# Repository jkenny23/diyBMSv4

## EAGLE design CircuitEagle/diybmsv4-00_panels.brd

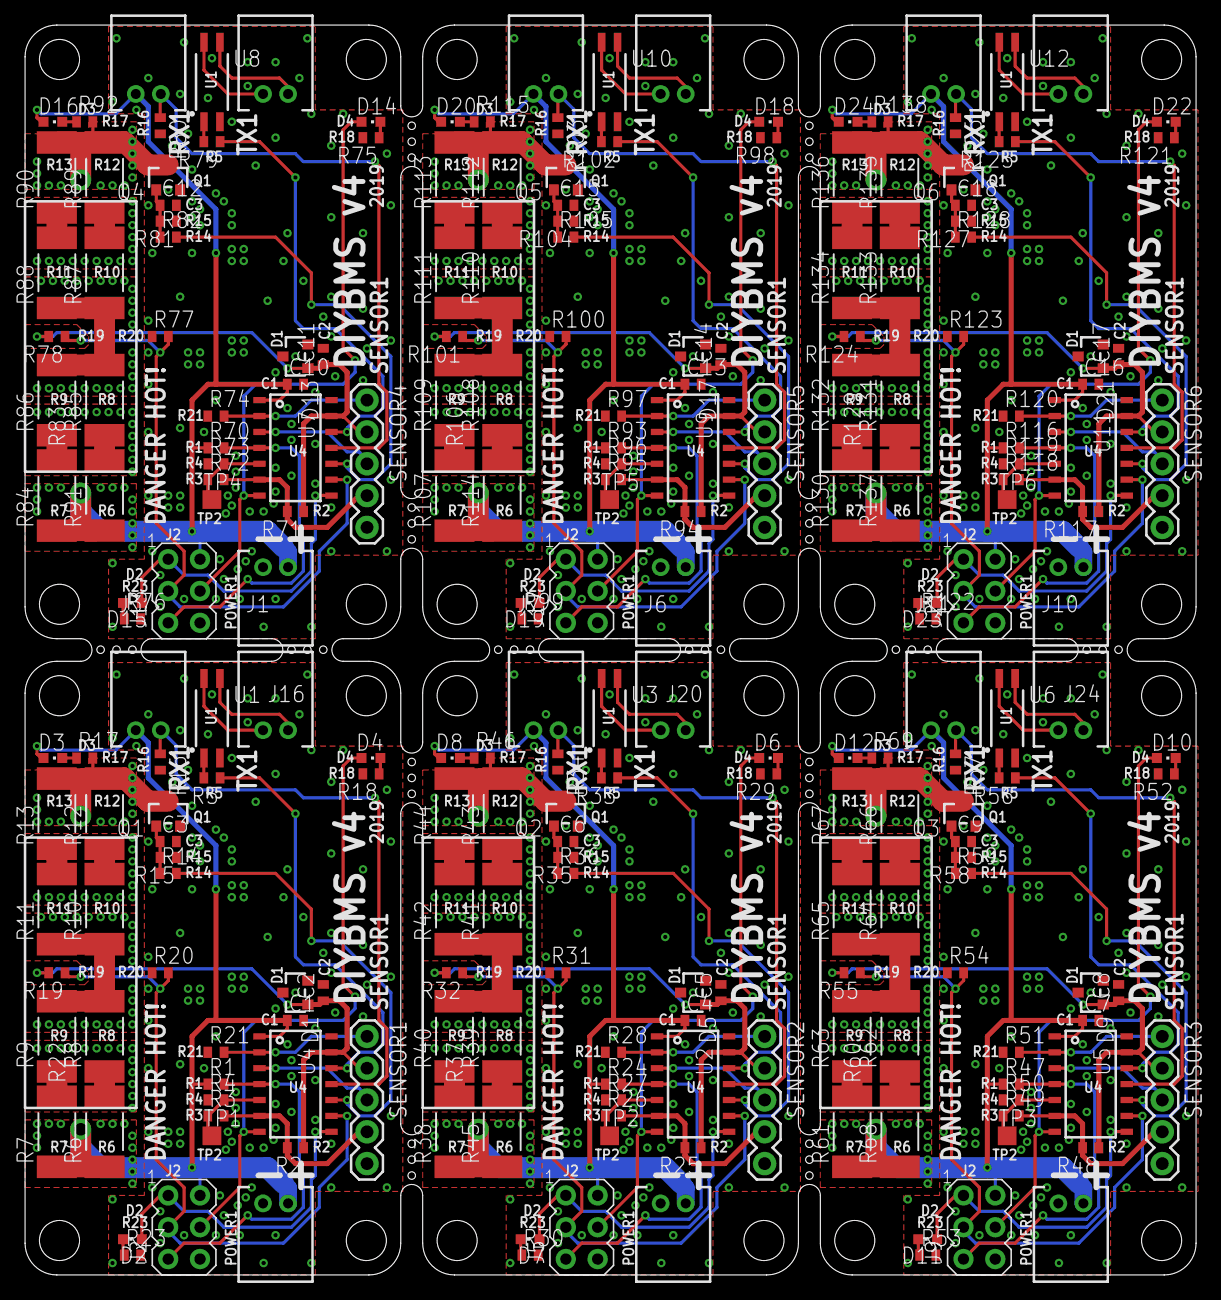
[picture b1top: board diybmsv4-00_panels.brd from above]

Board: 2 copper layers, 93.5 x 99.8 mm, 234 parts (0 on the bottom side), 150 nets.

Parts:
C1, C4, C7, C10, C13, C16: 100n; C0402
C2, C5, C8, C11, C14, C17: 2.2u; C0402
C3, C6, C9, C12, C15, C18: 10u/10V; C0402
D1, D5, D9, D13, D17, D21: LM4040; SOT23
D2, D7, D11, D15, D19, D23: Blue; CHIPLED_0603
D3, D8, D12, D16, D20, D24: Red; CHIPLED_0603
D4, D6, D10, D14, D18, D22: Green; CHIPLED_0603
J1, J3, J4, J6, J7, J8, J10, J11, J12, J14, J15, J16, J18, J19, J20, J22, J23, J24: M02PH; S2B-PH-RA
J2, J5, J9, J13, J17, J21: AVRISP-6; AVRISP
Q1, Q2, Q3, Q4, Q5, Q6: AO3400A; SOT23
R1, R24, R47, R70, R93, R116: 10k; R0402
R2, R25, R48, R71, R94, R117: 1k; R0402
R3, R26, R49, R72, R95, R118: 475k 1%; R0402
R4, R27, R50, R73, R96, R119: 402k 1%; R0402
R5, R14, R33, R36, R56, R59, R79, R82, R102, R105, R125, R128: 510; R0402
R6, R7, R8, R9, R10, R11, R12, R13, R38, R39, R40, R41, R42, R43, R44, R45, R61, R62, R63, R64, R65, R66, R67, R68, R84, R85, R86, R87, R88, R89, R90, R91, R107, R108, R109, R110, R111, R112, R113, R114, R130, R131, R132, R133, R134, R135, R136, R137: 2.2; R2512
R15, R20, R21, R28, R31, R35, R51, R54, R58, R74, R77, R81, R97, R100, R104, R120, R123, R127: 47k; R0402
R16, R34, R57, R80, R103, R126: 4.7k; R0402
R17, R18, R23, R29, R30, R46, R52, R53, R69, R75, R76, R92, R98, R99, R115, R121, R122, R138: 2.2k; R0402
R19, R32, R55, R78, R101, R124: NCP15WB473F03RC; R0402
R22, R37, R60, R83, R106, R129: 10 (DNI); R-5W-22X9P5X9P5
SENSOR1, SENSOR2, SENSOR3, SENSOR4, SENSOR5, SENSOR6: 1X05
TP1, TP2, TP3, TP4, TP5, TP6: TPTP15SQ; TP15SQ
U1, U3, U6, U8, U10, U12: HMHA2801; 4-SOIC
U2, U4, U5, U7, U9, U11: ATTINY841; 14-SOIC

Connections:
2_VOLT: C2.1, D1.1, R2.1, R19.2, SENSOR1.2, U4.13
2_VOLT1: C5.1, D5.1, R25.1, R32.2, SENSOR2.2, U2.13
2_VOLT2: C8.1, D9.1, R48.1, R55.2, SENSOR3.2, U5.13
2_VOLT3: C11.1, D13.1, R71.1, R78.2, SENSOR4.2, U7.13
2_VOLT4: C14.1, D17.1, R94.1, R101.2, SENSOR5.2, U9.13
2_VOLT5: C17.1, D21.1, R117.1, R124.2, SENSOR6.2, U11.13
DLLED: D3.C, R17.1
DLLED1: D8.C, R46.1
DLLED2: D12.C, R69.1
DLLED3: D16.C, R92.1
DLLED4: D20.C, R115.1
DLLED5: D24.C, R138.1
DRAIN: Q1.3, R12.2, R13.2, R17.2, R22.2
DRAIN1: Q2.3, R37.2, R43.2, R44.2, R46.2
DRAIN2: Q3.3, R60.2, R66.2, R67.2, R69.2
DRAIN3: Q4.3, R83.2, R89.2, R90.2, R92.2
DRAIN4: Q5.3, R106.2, R112.2, R113.2, R115.2
DRAIN5: Q6.3, R129.2, R135.2, R136.2, R138.2
DUMP_LOAD_ENABLE: R14.2, U4.10
DUMP_LOAD_ENABLE1: R36.2, U2.10
DUMP_LOAD_ENABLE2: R59.2, U5.10
DUMP_LOAD_ENABLE3: R82.2, U7.10
DUMP_LOAD_ENABLE4: R105.2, U9.10
DUMP_LOAD_ENABLE5: R128.2, U11.10
ENABLE: R2.2, R3.2, SENSOR1.4, U4.6
ENABLE1: R25.2, R26.2, SENSOR2.4, U2.6
ENABLE2: R48.2, R49.2, SENSOR3.4, U5.6
ENABLE3: R71.2, R72.2, SENSOR4.4, U7.6
ENABLE4: R94.2, R95.2, SENSOR5.4, U9.6
ENABLE5: R117.2, R118.2, SENSOR6.4, U11.6
GATE: C3.1, Q1.1, R14.1, R15.2
GATE1: C6.1, Q2.1, R35.2, R36.1
GATE2: C9.1, Q3.1, R58.2, R59.1
GATE3: C12.1, Q4.1, R81.2, R82.1
GATE4: C15.1, Q5.1, R104.2, R105.1
GATE5: C18.1, Q6.1, R127.2, R128.1
GND: C1.2, C2.2, C3.2, D1.2, J2.6, J4.2, Q1.2, R4.1, R15.1, R16.2, R18.2, R20.1, R21.1, R23.2, SENSOR1.5, U1.2, U4.14
GND1: C4.2, C5.2, C6.2, D5.2, J5.6, J8.2, Q2.2, R27.1, R28.1, R29.2, R30.2, R31.1, R34.2, R35.1, SENSOR2.5, U2.14, U3.2
GND2: C7.2, C8.2, C9.2, D9.2, J9.6, J12.2, Q3.2, R50.1, R51.1, R52.2, R53.2, R54.1, R57.2, R58.1, SENSOR3.5, U5.14, U6.2
GND3: C10.2, C11.2, C12.2, D13.2, J13.6, J16.2, Q4.2, R73.1, R74.1, R75.2, R76.2, R77.1, R80.2, R81.1, SENSOR4.5, U7.14, U8.2
GND4: C13.2, C14.2, C15.2, D17.2, J17.6, J20.2, Q5.2, R96.1, R97.1, R98.2, R99.2, R100.1, R103.2, R104.1, SENSOR5.5, U9.14, U10.2
GND5: C16.2, C17.2, C18.2, D21.2, J21.6, J24.2, Q6.2, R119.1, R120.1, R121.2, R122.2, R123.1, R126.2, R127.1, SENSOR6.5, U11.14, U12.2
MISO: D2.A, J2.1, U4.8
MISO1: D7.A, J5.1, U2.8
MISO2: D11.A, J9.1, U5.8
MISO3: D15.A, J13.1, U7.8
MISO4: D19.A, J17.1, U9.8
MISO5: D23.A, J21.1, U11.8
MOSI: D4.A, J2.4, U4.7
MOSI1: D6.A, J5.4, U2.7
MOSI2: D10.A, J9.4, U5.7
MOSI3: D14.A, J13.4, U7.7
MOSI4: D18.A, J17.4, U9.7
MOSI5: D22.A, J21.4, U11.7
unnamed: J1.1, U1.4
unnamed: J1.2, U1.3
unnamed: D4.C, R18.1
unnamed: D2.C, R23.1
unnamed: R5.2, U1.1
unnamed: D6.C, R29.1
unnamed: D7.C, R30.1
unnamed: J6.1, U3.4
unnamed: J6.2, U3.3
unnamed: R33.2, U3.1
unnamed: D10.C, R52.1
unnamed: D11.C, R53.1
unnamed: J10.1, U6.4
unnamed: J10.2, U6.3
unnamed: R56.2, U6.1
unnamed: D14.C, R75.1
unnamed: D15.C, R76.1
unnamed: J14.1, U8.4
unnamed: J14.2, U8.3
unnamed: R79.2, U8.1
unnamed: D18.C, R98.1
unnamed: D19.C, R99.1
unnamed: J18.1, U10.4
unnamed: J18.2, U10.3
unnamed: R102.2, U10.1
unnamed: D22.C, R121.1
unnamed: D23.C, R122.1
unnamed: J22.1, U12.4
unnamed: J22.2, U12.3
unnamed: R125.2, U12.1
PB0: R21.2, SENSOR1.1, U4.2
PB1: SENSOR1.3, U4.3
PB2: R3.1, R4.2, TP1.TP, U4.5
PB3: R26.1, R27.2, TP2.TP, U2.5
PB4: R28.2, SENSOR2.1, U2.2
PB5: SENSOR2.3, U2.3
PB6: R49.1, R50.2, TP3.TP, U5.5
PB7: R51.2, SENSOR3.1, U5.2
PB8: SENSOR3.3, U5.3
PB9: R72.1, R73.2, TP4.TP, U7.5
PB10: R74.2, SENSOR4.1, U7.2
PB11: SENSOR4.3, U7.3
PB12: R95.1, R96.2, TP5.TP, U9.5
PB13: R97.2, SENSOR5.1, U9.2
PB14: SENSOR5.3, U9.3
PB15: R118.1, R119.2, TP6.TP, U11.5
PB16: R120.2, SENSOR6.1, U11.2
PB17: SENSOR6.3, U11.3
R1: R39.2, R40.2, R41.1, R42.1
R2: R41.2, R42.2, R43.1, R44.1
R3: R38.2, R39.1, R40.1, R45.2
R4: R62.2, R63.2, R64.1, R65.1
R5: R64.2, R65.2, R66.1, R67.1
R6: R61.2, R62.1, R63.1, R68.2
R7: R85.2, R86.2, R87.1, R88.1
R8: R87.2, R88.2, R89.1, R90.1
R9: R84.2, R85.1, R86.1, R91.2
R10: R108.2, R109.2, R110.1, R111.1
R11: R110.2, R111.2, R112.1, R113.1
R12: R107.2, R108.1, R109.1, R114.2
R13: R131.2, R132.2, R133.1, R134.1
R14: R133.2, R134.2, R135.1, R136.1
R15: R130.2, R131.1, R132.1, R137.2
R6789: R6.2, R7.2, R8.1, R9.1
R891011: R8.2, R9.2, R10.1, R11.1
R10111213: R10.2, R11.2, R12.1, R13.1
RST: J2.5, R1.2, U4.4
RST1: J5.5, R24.2, U2.4
RST2: J9.5, R47.2, U5.4
RST3: J13.5, R70.2, U7.4
RST4: J17.5, R93.2, U9.4
RST5: J21.5, R116.2, U11.4
RXD0: J3.2, R16.1, U4.11
RXD1: J7.2, R34.1, U2.11
RXD2: J11.2, R57.1, U5.11
RXD3: J15.2, R80.1, U7.11
RXD4: J19.2, R103.1, U9.11
RXD5: J23.2, R126.1, U11.11
SCK: J2.3, R19.1, R20.2, U4.9
SCK1: J5.3, R31.2, R32.1, U2.9
SCK2: J9.3, R54.2, R55.1, U5.9
SCK3: J13.3, R77.2, R78.1, U7.9
SCK4: J17.3, R100.2, R101.1, U9.9
SCK5: J21.3, R123.2, R124.1, U11.9
TXD0: R5.1, U4.12
TXD1: R33.1, U2.12
TXD2: R56.1, U5.12
TXD3: R79.1, U7.12
TXD4: R102.1, U9.12
TXD5: R125.1, U11.12
VCC: C1.1, D3.A, J2.2, J3.1, J4.1, R1.1, R6.1, R7.1, R22.1, U4.1
VCC1: C4.1, D8.A, J5.2, J7.1, J8.1, R24.1, R37.1, R38.1, R45.1, U2.1
VCC2: C7.1, D12.A, J9.2, J11.1, J12.1, R47.1, R60.1, R61.1, R68.1, U5.1
VCC3: C10.1, D16.A, J13.2, J15.1, J16.1, R70.1, R83.1, R84.1, R91.1, U7.1
VCC4: C13.1, D20.A, J17.2, J19.1, J20.1, R93.1, R106.1, R107.1, R114.1, U9.1
VCC5: C16.1, D24.A, J21.2, J23.1, J24.1, R116.1, R129.1, R130.1, R137.1, U11.1

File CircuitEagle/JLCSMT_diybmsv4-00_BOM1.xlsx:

Comment | Designator | Footprint | LCSC Part #（optional）
1kΩ | R2, R25, R48, R71, R94, R117 | 0402_R | C11702
2.2kΩ | R17, R18, R23, R29, R30, R46, R52, R53, R69, R75, R76, R92, R98, R99, R115, R12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 | 0402_R | C25879
2.2u | C2, C5, C8, C11, C14, C17 | 0402_C | C12530 | ext
4.7kΩ | R16, R34, R57, R80, R103, R126 | 0402_R | C25900
10kΩ | R1, R24, R47, R70, R93, R116 | 0402_R | C25744
10u/10V | C3, C6, C9, C12, C15, C18 | 0603_C | C19702
47kΩ | R15, R20, R21, R28, R31, R35, R51, R54, R58, R74, R77, R81, R97, R100, R104, R1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 | 0402_R | C25792
100n | C1, C4, C7, C10, C13, C16 | 0402_C | C1525
402kΩ 1% | R4, R27, R50, R73, R96, R119 | 0402_R | C25785 | ext
475kΩ 1% | R3, R26, R49, R72, R95, R118 | 0402_R | C25791 | ext
510Ω | R5, R14, R33, R36, R56, R59, R79, R82, R102, R105, R125, R128 | 0402_R | C25123
AO3400A | Q1, Q2, Q3, Q4, Q5, Q6 | SOT-23-3L | C20917
Blue | D2, D7, D11, D15, D19, D23 | 0603_LED | C72041
Green | D4, D6, D10, D14, D18, D22 | 0603_LED | C72043
HMHA2801 | U1, U3, U6, U8, U10, U12 | SOIC-4_2.5x4.4x1.27P | C258257 | ext
LM4040 | D1, D5, D9, D13, D17, D21 | SOT-23 | C48833 | ext
NCP15WB473F03RC | R19, R32, R55, R78, R101, R124 | 0402_R | C77128
Red | D3, D8, D12, D16, D20, D24 | 0603_LED | C40378

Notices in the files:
parts and their libraries:
SparkFun: Licensing: CC v3.0 Share-Alike You are welcome to use this library for commercial purposes.
